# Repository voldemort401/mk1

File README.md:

made for hack club's [fabricate](https://fabricate.hackclub.com)

Its a keyboard with 78 keys i quite like the keyboard it took me some time but i am happy with it i mean its my first electronics project so i am quite 
happy with the final product 

It has these features
- 78 keys
- reprogram anykey anyway you like using the keymap.c file located in the firmware/keymaps/default/keymap.c
- 1 rotary encoder
- a 128 x 32 OLED display
- and you can also kinda use this as a mouse

## Inspiration 
I made this project because i was inspired by the [brew-keeb](https://github.com/geg-tech/brew-keeb) project of [geg-tech](https://github.com/geg-tech) i really liked his keyboard and i also wanted to make my own keyboard so 
i thank geg-tech for making an awesome project and giving me the inspiration to make this one!!

## CAD

## Schematic + PCB

## Usage of AI in this project 
During this project, I used AI to help with debugging KiCad DRC errors and i also used it to learn how to create those cutouts precisely but the designs were done by hand by me with no use from ai

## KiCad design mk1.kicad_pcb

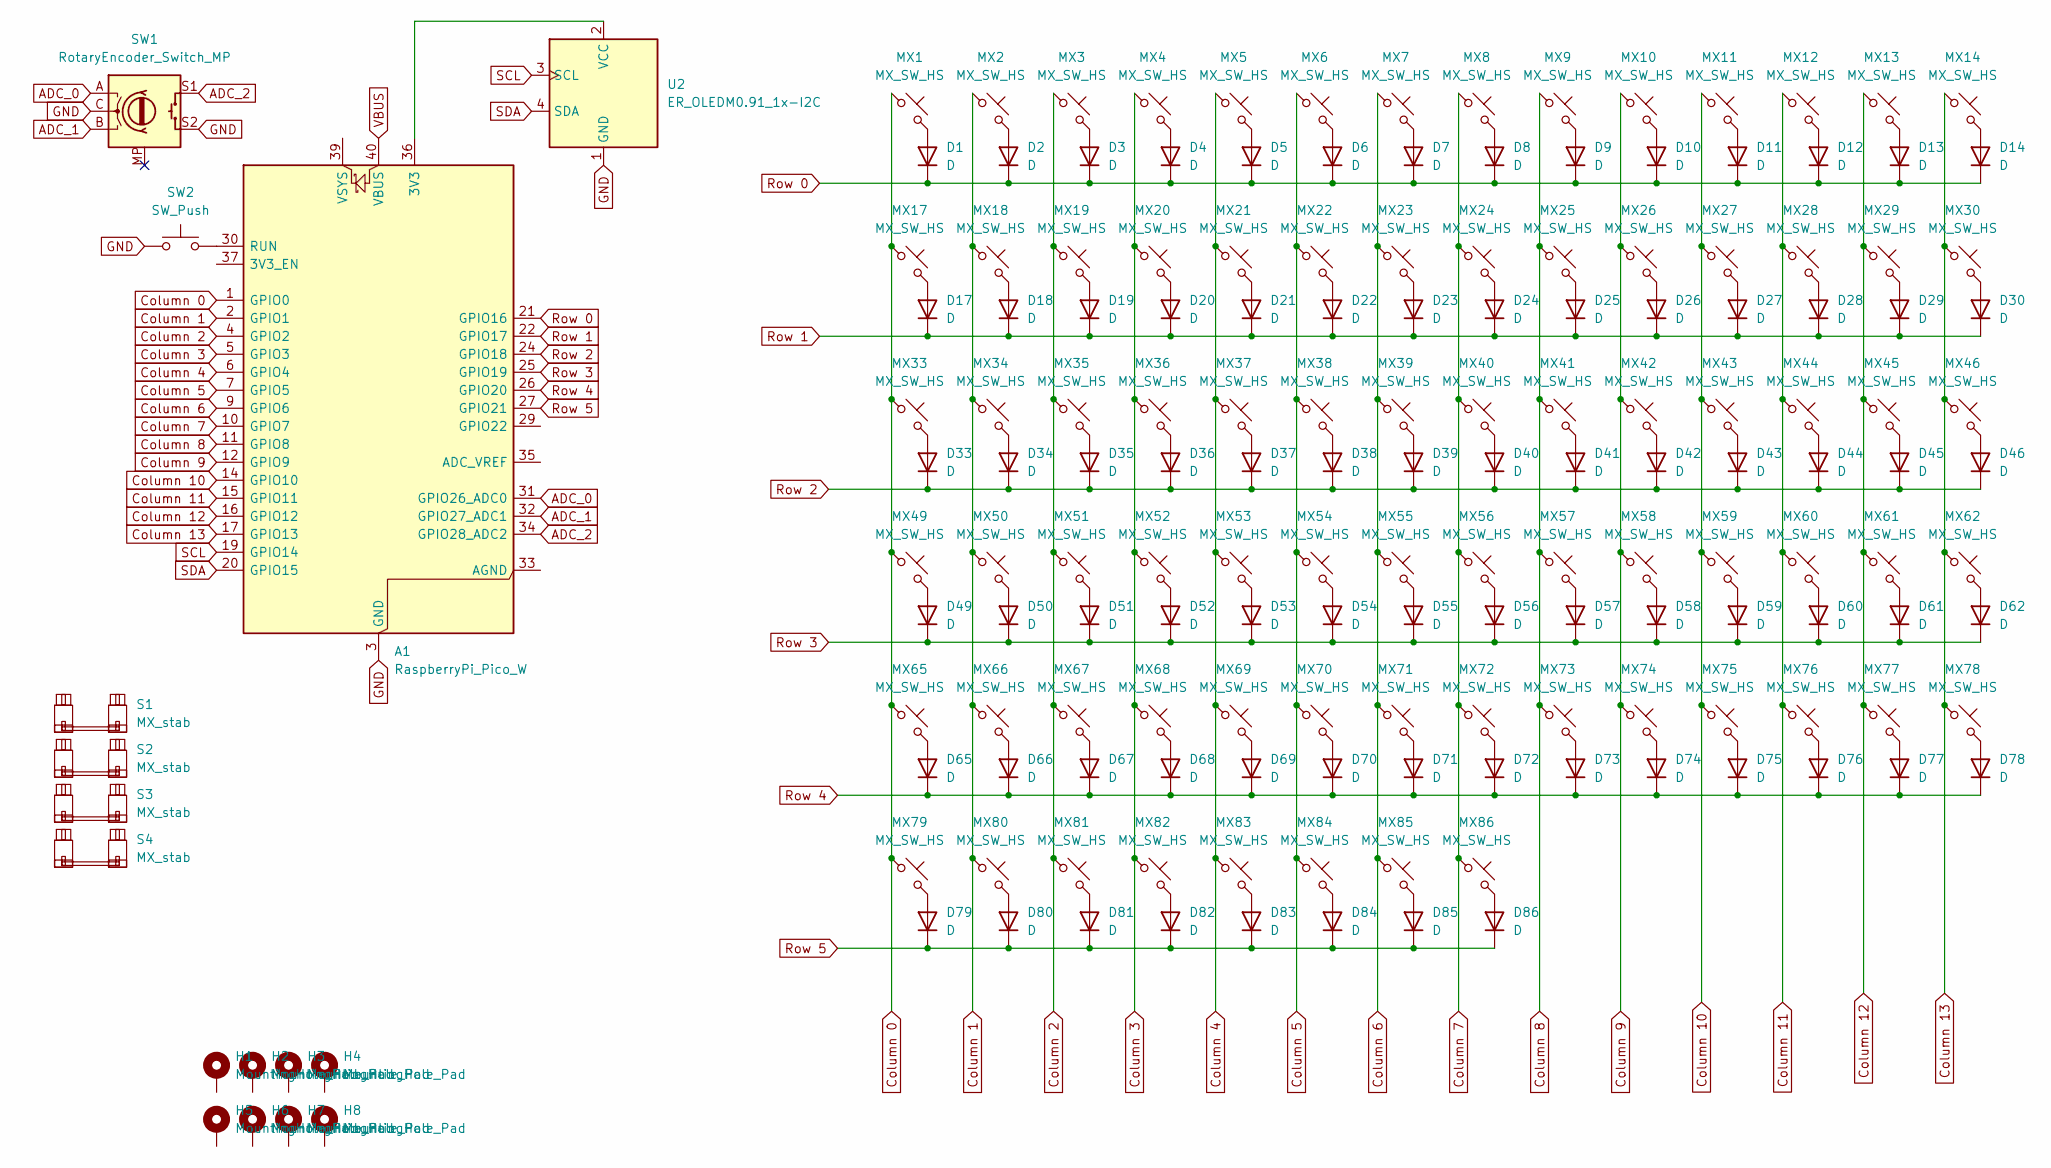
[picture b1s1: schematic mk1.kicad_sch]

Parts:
A1: RaspberryPi_Pico_W; RaspberryPi_Pico_W_SMD_HandSolder
D1, D2, D3, D4, D5, D6, D7, D8, D9, D10, D11, D12, D13, D14, D17, D18, D19, D20, D21, D22, D23, D24, D25, D26, D27, D28, D29, D30, D33, D34, D35, D36, D37, D38, D39, D40, D41, D42, D43, D44, D45, D46, D49, D50, D51, D52, D53, D54, D55, D56, D57, D58, D59, D60, D61, D62, D65, D66, D67, D68, D69, D70, D71, D72, D73, D74, D75, D76, D77, D78, D79, D80, D81, D82, D83, D84, D85, D86: D; D_SOD-123
H1, H2, H3, H4, H5, H6, H7, H8: MountingHole_Pad; MountingHole_3.2mm_M3_Pad
MX1, MX2, MX3, MX4, MX5, MX6, MX7, MX8, MX9, MX10, MX11, MX12, MX13, MX14, MX17, MX18, MX19, MX20, MX21, MX22, MX23, MX24, MX25, MX26, MX27, MX28, MX29, MX30, MX33, MX34, MX35, MX36, MX37, MX38, MX39, MX40, MX41, MX42, MX43, MX44, MX45, MX46, MX49, MX50, MX51, MX52, MX53, MX54, MX55, MX56, MX57, MX58, MX59, MX60, MX61, MX62, MX65, MX66, MX67, MX68, MX69, MX70, MX71, MX72, MX73, MX74, MX75, MX76, MX77, MX78, MX79, MX80, MX81, MX82, MX83, MX84, MX85, MX86: MX_SW_HS; SW_Cherry_MX_PCB_1.00u
S1: MX_stab; Stabilizer_Cherry_MX_6.25u
S2, S3, S4: MX_stab; Stabilizer_Cherry_MX_2.00u
SW1: RotaryEncoder_Switch_MP; ROT_Alps_EC11E-Switch
SW2: SW_Push; SW_PUSH_6mm
U2: ER_OLEDM0.91_1x-I2C

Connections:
ADC_0: A1.31 (GPIO26_ADC0), SW1.A
ADC_1: A1.32 (GPIO27_ADC1), SW1.B
ADC_2: A1.34 (GPIO28_ADC2), SW1.S1
Column 0: A1.1 (GPIO0), MX1.1, MX17.1, MX33.1, MX49.1, MX65.1, MX79.1
Column 1: A1.2 (GPIO1), MX2.1, MX18.1, MX34.1, MX50.1, MX66.1, MX80.1
Column 2: A1.4 (GPIO2), MX3.1, MX19.1, MX35.1, MX51.1, MX67.1, MX81.1
Column 3: A1.5 (GPIO3), MX4.1, MX20.1, MX36.1, MX52.1, MX68.1, MX82.1
Column 4: A1.6 (GPIO4), MX5.1, MX21.1, MX37.1, MX53.1, MX69.1, MX83.1
Column 5: A1.7 (GPIO5), MX6.1, MX22.1, MX38.1, MX54.1, MX70.1, MX84.1
Column 6: A1.9 (GPIO6), MX7.1, MX23.1, MX39.1, MX55.1, MX71.1, MX85.1
Column 7: A1.10 (GPIO7), MX8.1, MX24.1, MX40.1, MX56.1, MX72.1, MX86.1
Column 8: A1.11 (GPIO8), MX9.1, MX25.1, MX41.1, MX57.1, MX73.1; also elsewhere on the board
Column 9: A1.12 (GPIO9), MX10.1, MX26.1, MX42.1, MX58.1, MX74.1
Column 10: A1.14 (GPIO10), MX11.1, MX27.1, MX43.1, MX59.1, MX75.1
Column 11: A1.15 (GPIO11), MX12.1, MX28.1, MX44.1, MX60.1, MX76.1
Column 12: A1.16 (GPIO12), MX13.1, MX29.1, MX45.1, MX61.1, MX77.1
Column 13: A1.17 (GPIO13), MX14.1, MX30.1, MX46.1, MX62.1, MX78.1
GND: A1.3 (GND), A1.8 (GND), A1.13 (GND), A1.18 (GND), A1.23 (GND), A1.28 (GND), A1.38 (GND), SW1.C, SW1.S2, SW2.1, U2.1 (GND)
unnamed: A1.36 (3V3), U2.2 (VCC)
unnamed: A1.30 (RUN), SW2.2
unnamed: D1.2 (A), MX1.2
unnamed: D2.2 (A), MX2.2
unnamed: D3.2 (A), MX3.2
unnamed: D4.2 (A), MX4.2
unnamed: D5.2 (A), MX5.2
unnamed: D6.2 (A), MX6.2
unnamed: D7.2 (A), MX7.2
unnamed: D8.2 (A), MX8.2
unnamed: D9.2 (A), MX9.2
unnamed: D10.2 (A), MX10.2
unnamed: D11.2 (A), MX11.2
unnamed: D12.2 (A), MX12.2
unnamed: D13.2 (A), MX13.2
unnamed: D14.2 (A), MX14.2
unnamed: D17.2 (A), MX17.2
unnamed: D18.2 (A), MX18.2
unnamed: D19.2 (A), MX19.2
unnamed: D20.2 (A), MX20.2
unnamed: D21.2 (A), MX21.2
unnamed: D22.2 (A), MX22.2
unnamed: D23.2 (A), MX23.2
unnamed: D24.2 (A), MX24.2
unnamed: D25.2 (A), MX25.2
unnamed: D26.2 (A), MX26.2
unnamed: D27.2 (A), MX27.2
unnamed: D28.2 (A), MX28.2
unnamed: D29.2 (A), MX29.2
unnamed: D30.2 (A), MX30.2
unnamed: D33.2 (A), MX33.2
unnamed: D34.2 (A), MX34.2
unnamed: D35.2 (A), MX35.2
unnamed: D36.2 (A), MX36.2
unnamed: D37.2 (A), MX37.2
unnamed: D38.2 (A), MX38.2
unnamed: D39.2 (A), MX39.2
unnamed: D40.2 (A), MX40.2
unnamed: D41.2 (A), MX41.2
unnamed: D42.2 (A), MX42.2
unnamed: D43.2 (A), MX43.2
unnamed: D44.2 (A), MX44.2
unnamed: D45.2 (A), MX45.2
unnamed: D46.2 (A), MX46.2
unnamed: D49.2 (A), MX49.2
unnamed: D50.2 (A), MX50.2
unnamed: D51.2 (A), MX51.2
unnamed: D52.2 (A), MX52.2
unnamed: D53.2 (A), MX53.2
unnamed: D54.2 (A), MX54.2
unnamed: D55.2 (A), MX55.2
unnamed: D56.2 (A), MX56.2
unnamed: D57.2 (A), MX57.2
unnamed: D58.2 (A), MX58.2
unnamed: D59.2 (A), MX59.2
unnamed: D60.2 (A), MX60.2
unnamed: D61.2 (A), MX61.2
unnamed: D62.2 (A), MX62.2
unnamed: D65.2 (A), MX65.2
unnamed: D66.2 (A), MX66.2
unnamed: D67.2 (A), MX67.2
unnamed: D68.2 (A), MX68.2
unnamed: D69.2 (A), MX69.2
unnamed: D70.2 (A), MX70.2
unnamed: D71.2 (A), MX71.2
unnamed: D72.2 (A), MX72.2
unnamed: D73.2 (A), MX73.2
unnamed: D74.2 (A), MX74.2
unnamed: D75.2 (A), MX75.2
unnamed: D76.2 (A), MX76.2
unnamed: D77.2 (A), MX77.2
unnamed: D78.2 (A), MX78.2
unnamed: D79.2 (A), MX79.2
unnamed: D80.2 (A), MX80.2
unnamed: D81.2 (A), MX81.2
unnamed: D82.2 (A), MX82.2
unnamed: D83.2 (A), MX83.2
unnamed: D84.2 (A), MX84.2
unnamed: D85.2 (A), MX85.2
unnamed: D86.2 (A), MX86.2
Row 0: A1.21 (GPIO16), D1.1 (K), D2.1 (K), D3.1 (K), D4.1 (K), D5.1 (K), D6.1 (K), D7.1 (K), D8.1 (K), D9.1 (K), D10.1 (K), D11.1 (K), D12.1 (K), D13.1 (K), D14.1 (K)
Row 1: A1.22 (GPIO17), D17.1 (K), D18.1 (K), D19.1 (K), D20.1 (K), D21.1 (K), D22.1 (K), D23.1 (K), D24.1 (K), D25.1 (K), D26.1 (K), D27.1 (K), D28.1 (K), D29.1 (K), D30.1 (K)
Row 2: A1.24 (GPIO18), D33.1 (K), D34.1 (K), D35.1 (K), D36.1 (K), D37.1 (K), D38.1 (K), D39.1 (K), D40.1 (K), D41.1 (K), D42.1 (K), D43.1 (K), D44.1 (K), D45.1 (K), D46.1 (K)
Row 3: A1.25 (GPIO19), D49.1 (K), D50.1 (K), D51.1 (K), D52.1 (K), D53.1 (K), D54.1 (K), D55.1 (K), D56.1 (K), D57.1 (K), D58.1 (K), D59.1 (K), D60.1 (K), D61.1 (K), D62.1 (K)
Row 4: A1.26 (GPIO20), D65.1 (K), D66.1 (K), D67.1 (K), D68.1 (K), D69.1 (K), D70.1 (K), D71.1 (K), D72.1 (K), D73.1 (K), D74.1 (K), D75.1 (K), D76.1 (K), D77.1 (K), D78.1 (K)
Row 5: A1.27 (GPIO21), D79.1 (K), D80.1 (K), D81.1 (K), D82.1 (K), D83.1 (K), D84.1 (K), D85.1 (K), D86.1 (K); also elsewhere on the board
VBUS: A1.40 (VBUS)

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
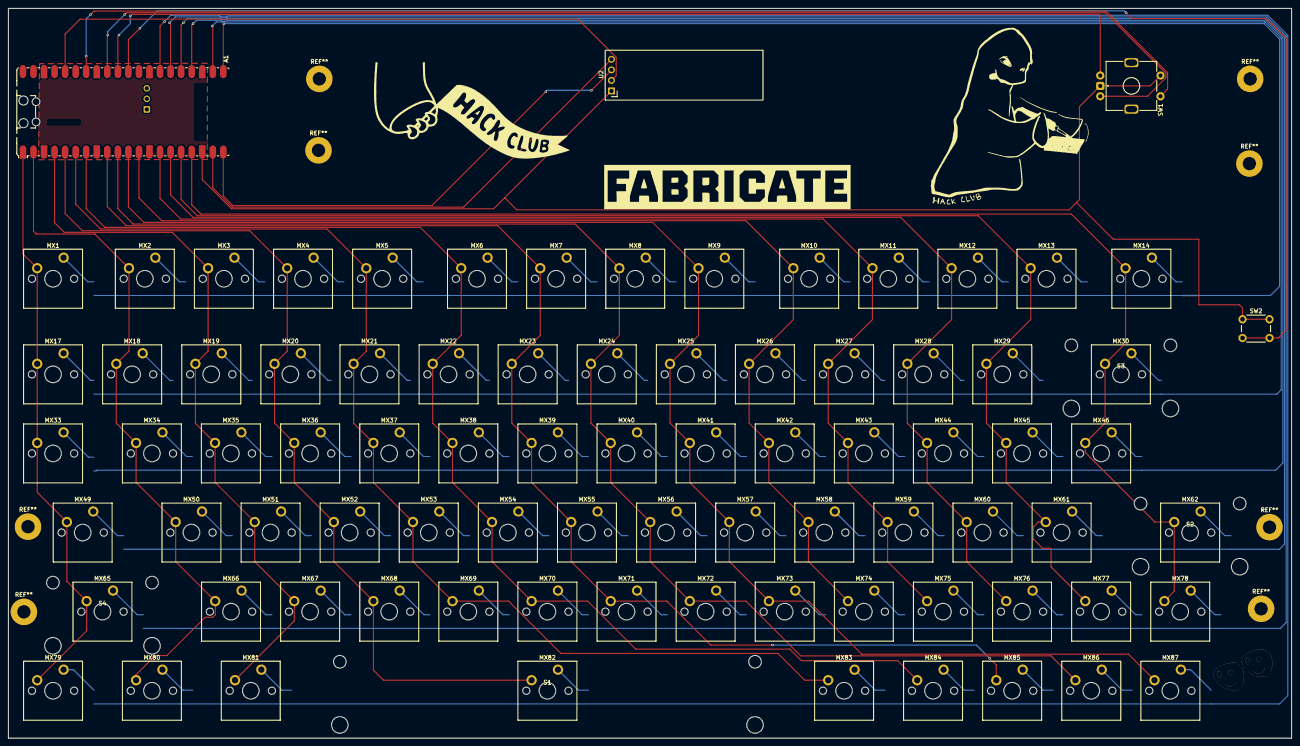
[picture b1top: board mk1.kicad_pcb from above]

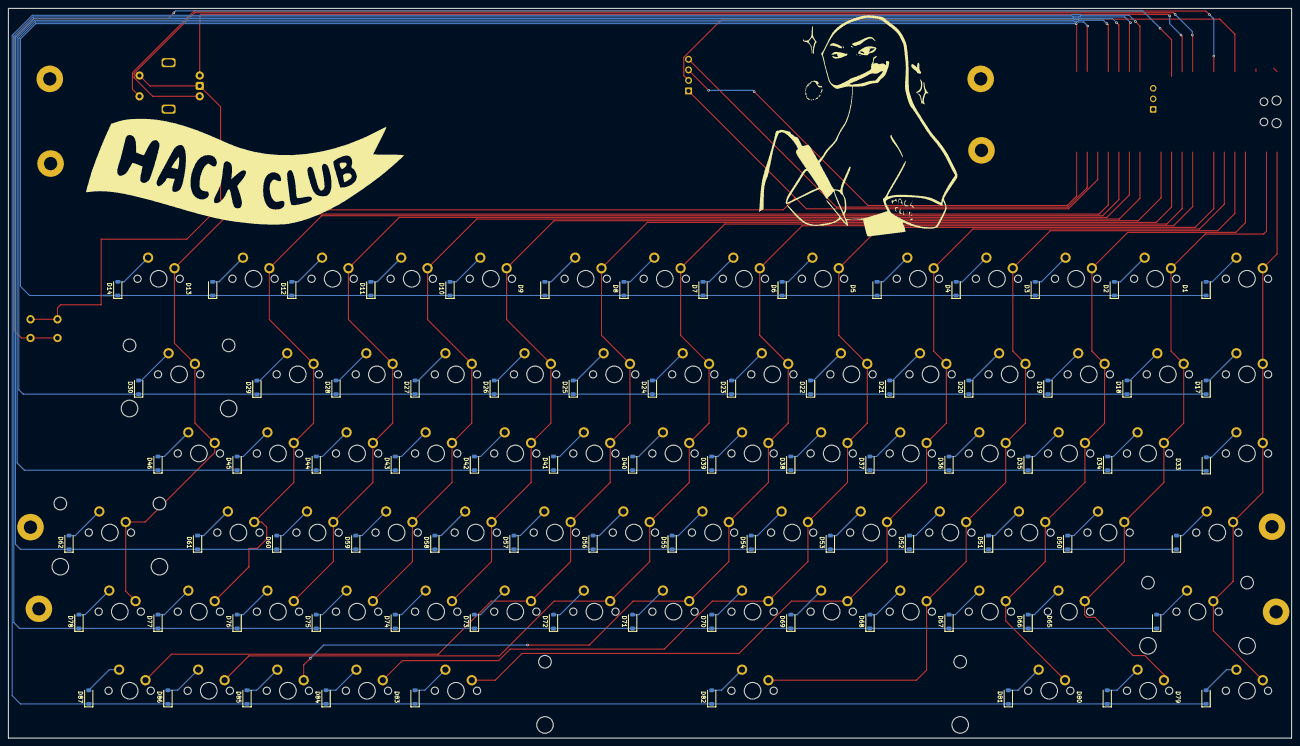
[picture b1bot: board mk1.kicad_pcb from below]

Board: 2 copper layers, 309.0 x 175.7 mm, 166 parts (79 on the bottom side), 107 nets.

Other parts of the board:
D87: D; D_SOD-123
MX87: MX_SW_HS; SW_Cherry_MX_PCB_1.00u

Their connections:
Column 8: MX87.1; also elsewhere on the board
unnamed: D87.2 (A), MX87.2
Row 5: D87.1 (K); also elsewhere on the board

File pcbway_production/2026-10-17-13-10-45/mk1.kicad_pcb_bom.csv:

Designator,Quantity,Value,Footprint,Package,MPN,DNP,Mount_Type,Description,Sim.Device,Sim.Pins
"D1, D10, D11, D12, D13, D14, D15, D16, D17, D18, D19, D2, D20, D21, D22, D23, D24, D25, D26, D27, D28, D29, D3, D30, D31, D32, D33, D34, D35, D36, D37, D38, D39, D4, D40, D41, D42, D43, D44, D45, D46, D47, D48, D49, D5, D50, D51, D52, D53, D54, D55, D56, D57, D58, D59, D6, D60, D7, D8, D9",60,D,D_SOD-123,,,,smt,Diode,D,1=K 2=A
"MX1, MX10, MX11, MX12, MX13, MX14, MX15, MX16, MX17, MX18, MX19, MX2, MX20, MX21, MX22, MX23, MX24, MX25, MX26, MX27, MX28, MX29, MX3, MX30, MX31, MX32, MX33, MX34, MX35, MX36, MX37, MX38, MX39, MX4, MX40, MX41, MX42, MX43, MX44, MX45, MX46, MX47, MX48, MX49, MX5, MX50, MX51, MX52, MX53, MX54, MX55, MX56, MX57, MX58, MX59, MX6, MX60, MX7, MX8, MX9",60,MX_SW_HS,SW_Cherry_MX_PCB_1.00u,,,,tht,"Push button switch, normally open, two pins, 45° tilted, Kailh CPG151101S11 for Cherry MX style switches",,
U2,1,ER_OLEDM0.91_1x-I2C,ER_OLEDM0.91_1x-I2C,,,,tht,"SSD1306 OLED module, 0.91 inch, 128x32, I2C",,
